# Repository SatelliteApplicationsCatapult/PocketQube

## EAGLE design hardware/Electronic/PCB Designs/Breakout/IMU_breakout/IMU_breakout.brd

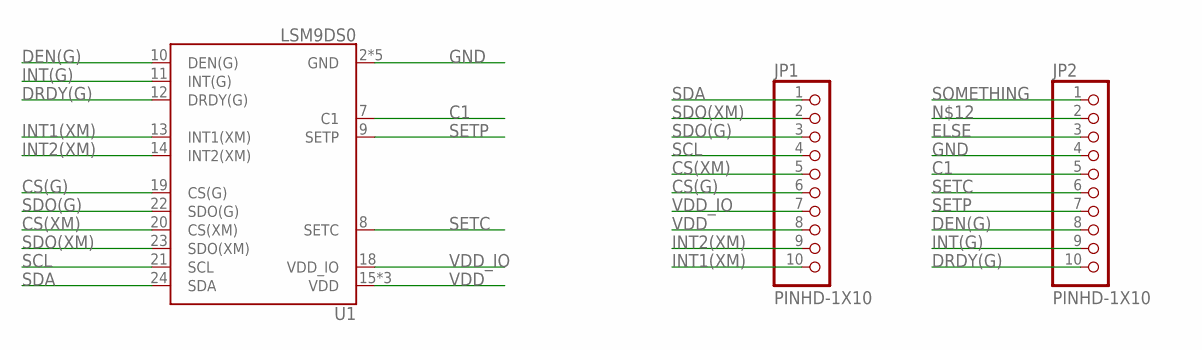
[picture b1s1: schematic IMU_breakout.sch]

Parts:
JP1, JP2: PINHD-1X10; 1X10-BIG
U1: LSM9DS0; LGA-24

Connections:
C1: JP2.5, U1.7 (C1)
CS(G): JP1.6, U1.19 (CS(G))
CS(XM): JP1.5, U1.20 (CS(XM))
DEN(G): JP2.8, U1.10 (DEN(G))
DRDY(G): JP2.10, U1.12 (DRDY(G))
ELSE: JP2.3
GND: JP2.4, U1.2 (GND), U1.3 (GND), U1.4 (GND), U1.5 (GND), U1.6 (GND)
INT1(XM): JP1.10, U1.13 (INT1(XM))
INT2(XM): JP1.9, U1.14 (INT2(XM))
INT(G): JP2.9, U1.11 (INT(G))
SCL: JP1.4, U1.21 (SCL)
SDA: JP1.1, U1.24 (SDA)
SDO(G): JP1.3, U1.22 (SDO(G))
SDO(XM): JP1.2, U1.23 (SDO(XM))
SETC: JP2.6, U1.8 (SETC)
SETP: JP2.7, U1.9 (SETP)
SOMETHING: JP2.1
VDD: JP1.8, U1.15 (VDD), U1.16 (VDD), U1.17 (VDD)
VDD_IO: JP1.7, U1.18 (VDD_IO)

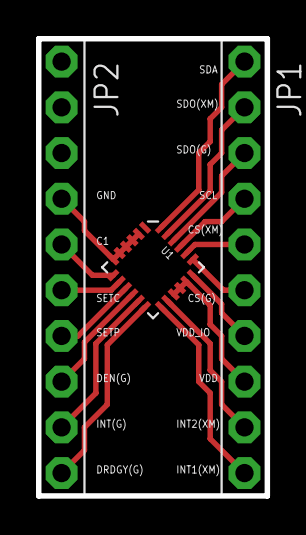
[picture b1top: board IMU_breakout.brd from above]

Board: 2 copper layers, 12.7 x 25.4 mm, 3 parts (0 on the bottom side), 17 nets.

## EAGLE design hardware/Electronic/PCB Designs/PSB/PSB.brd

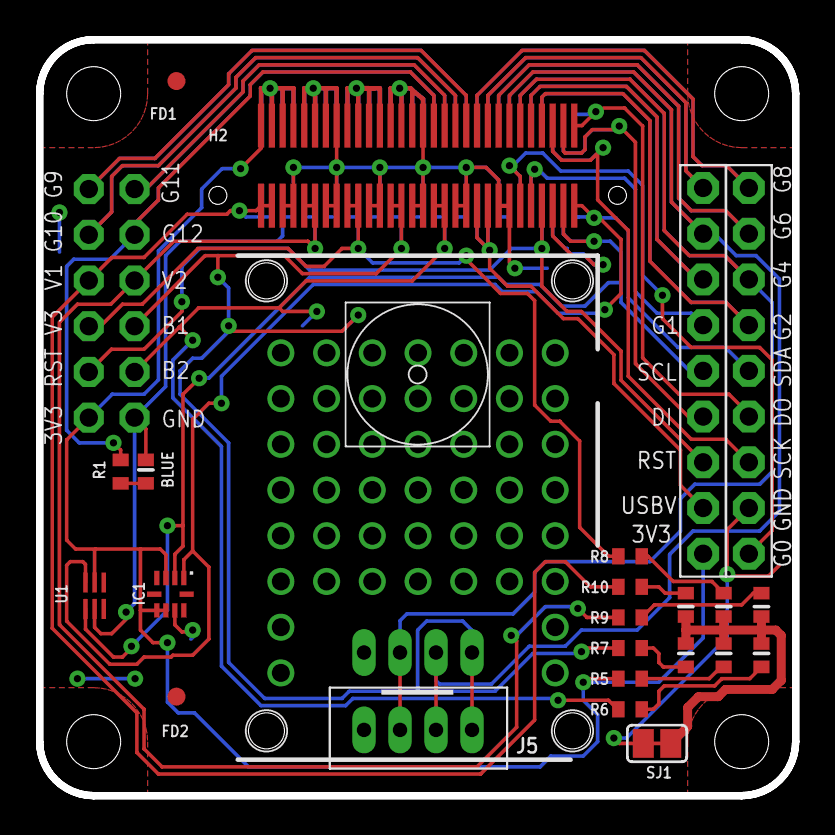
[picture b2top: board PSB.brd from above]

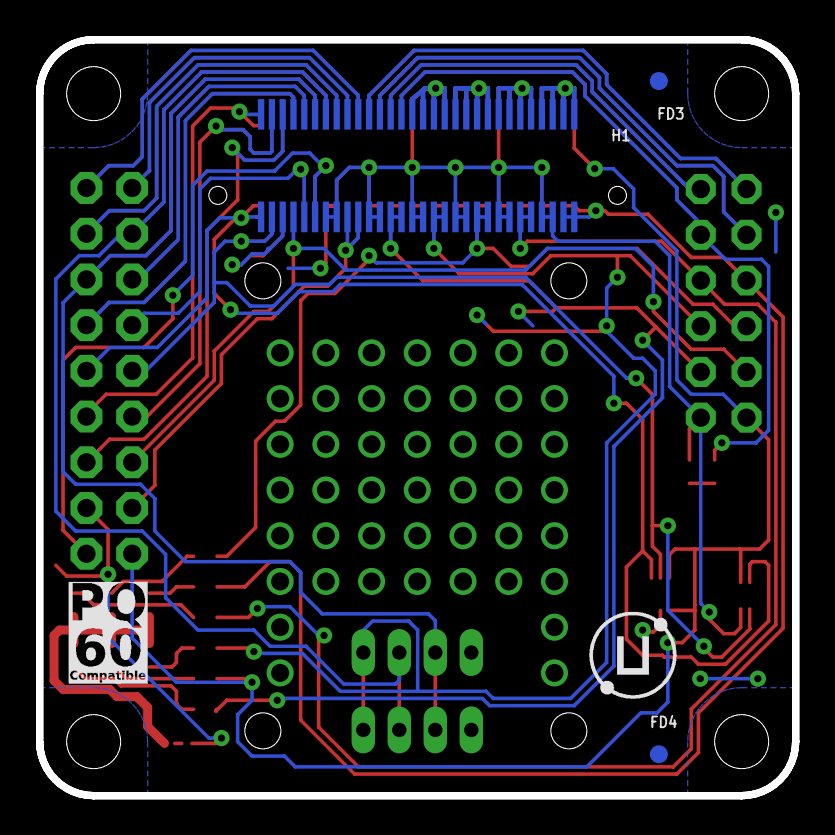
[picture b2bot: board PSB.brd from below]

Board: 2 copper layers, 42.0 x 42.0 mm, 31 parts (5 on the bottom side), 36 nets.

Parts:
BLUE: LED-0402; 0402-LED
FD1, FD2, FD3, FD4: FIDUCIAL; FIDUCIAL_1MM
GREEB@2: LED-0402; 0402-LED
GREEN@1, GREEN@3: LED-0402; 0402-LED
H1: FX8C-060S-SV(92)
H2: FX8C-060P-SV(92)
IC1: SI1146; QFN-10
J5, J6: JST-PH_4-PIN_HEADER; JST_B4B-PH_HEADER
JP1: 2X06-CLEANBIG
JP2, JP5: 1X09-BIG
R1, R5, R8, R9, R10: 220R; R0402
R6, R7: 330R; R0402
RED: LED-0402; 0402-LED
SJ1: SJ
U1: TMP102AIDRLT; SOT50P160X60-6N
U$1: SA_LOGO_SMALL
U$2: UBO_LOGO
U$3: PQ60_CMP
YELLOW@1, YELLOW@2: LED-0402; 0402-LED

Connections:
+3V3: H1.P$57, H1.P$58, H1.P$59, H1.P$60, H2.P$57, H2.P$58, H2.P$59, H2.P$60, IC1.3, IC1.6, IC1.7, JP1.11, JP5.9, R5.2, U1.5
+3V3_SW1: H1.P$1, H1.P$2, H2.P$1, H2.P$2, JP1.5, R10.2
+3V3_SW2: H1.P$5, H1.P$6, H2.P$5, H2.P$6, JP1.6, R9.2
+3V3_SW3: H1.P$9, H1.P$10, H2.P$9, H2.P$10, JP1.7, R8.2
BATV: H1.P$49, H1.P$50, H1.P$51, H1.P$52, H2.P$49, H2.P$50, H2.P$51, H2.P$52
BATV_SW1: H1.P$13, H1.P$14, H2.P$13, H2.P$14, J5.P4, J6.P4, JP1.8, R7.2
BATV_SW2: H1.P$17, H1.P$18, H2.P$17, H2.P$18, JP1.10, R6.2
GND: BLUE.C, H1.P$3, H1.P$4, H1.P$7, H1.P$8, H1.P$11, H1.P$12, H1.P$15, H1.P$16, H1.P$19, H1.P$20, H1.P$23, H1.P$24, H1.P$28, H1.P$45, H1.P$46, H1.P$47, H1.P$48, H1.P$53, H1.P$54, H1.P$55, H1.P$56, H2.P$3, H2.P$4, H2.P$7, H2.P$8, H2.P$11, H2.P$12, H2.P$15, H2.P$16, H2.P$19, H2.P$20, H2.P$23, H2.P$24, H2.P$28, H2.P$45, H2.P$46, H2.P$47, H2.P$48, H2.P$53, H2.P$54, H2.P$55, H2.P$56, IC1.8, J5.P1, J6.P1, JP1.12, JP2.8, SJ1.2, U1.2, U1.4
GPIO0: H1.P$25, H2.P$25, JP2.9
GPIO1: H1.P$26, H2.P$26, JP5.4
GPIO2: H1.P$34, H2.P$34, JP2.4
GPIO3: H1.P$35, H2.P$35, JP5.3
GPIO4: H1.P$36, H2.P$36, J5.P2, J6.P2, JP2.3
GPIO5: H1.P$37, H2.P$37, J5.P3, J6.P3, JP5.2
GPIO6: H1.P$38, H2.P$38, JP2.2
GPIO7: H1.P$39, H2.P$39, JP5.1
GPIO8: H1.P$40, H2.P$40, JP2.1
GPIO9: H1.P$41, H2.P$41, JP1.1
GPIO10: H1.P$42, H2.P$42, JP1.3
GPIO11: H1.P$43, H2.P$43, JP1.2
GPIO12: H1.P$44, H2.P$44, JP1.4, R1.2
MISO: H1.P$32, H2.P$32, JP5.6
MOSI: H1.P$31, H2.P$31, JP2.6
unnamed: BLUE.A, R1.1
unnamed: GREEN@1.A, R10.1
unnamed: GREEB@2.A, R9.1
unnamed: GREEN@3.A, R8.1
unnamed: R7.1, YELLOW@1.A
unnamed: R6.1, YELLOW@2.A
unnamed: R5.1, RED.A
unnamed: GREEB@2.C, GREEN@1.C, GREEN@3.C, RED.C, SJ1.1, YELLOW@1.C, YELLOW@2.C
RESET: H1.P$27, H2.P$27, JP1.9, JP5.7
SCK: H1.P$33, H2.P$33, JP2.7
SCL: H1.P$29, H2.P$29, IC1.2, JP5.5, U1.1
SDA: H1.P$30, H2.P$30, IC1.1, JP2.5, U1.6
USB_VBUS: H1.P$21, H1.P$22, H2.P$21, H2.P$22, JP5.8

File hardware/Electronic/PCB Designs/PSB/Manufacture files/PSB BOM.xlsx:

Qty | Value | Device | Package | Parts | Description | Supplier | Order code | Price per | Total | Notes
2 |  | PINHD-1X9 | 1X09-BIG | JP2, JP5 | Pin header 1x10 0.1 spacing" |  |  |  | 0 | Do not populate
1 |  | PINHD-2X6 | 2X06-CLEANBIG | JP1 | PIN HEADER |  |  |  | 0 | Do not populate
1 |  | SJ | SJ | SJ1 | SMD solder JUMPER |  |  |  | 0 | Do not populate
5 | 220R | R-EU_R0402 | R0402 | R1, R5, R8, R9, R10 | RESISTOR, European symbol |  |  |  | 0
2 | 330R | R-EU_R0402 | R0402 | R6, R7 | RESISTOR, European symbol |  |  |  | 0
4 | FIDUCIAL | FIDUCIAL | FIDUCIAL_1MM | FD1, FD2, FD3, FD4 | For use by pick and place machines to calibrate the vision/machine, 1mm |  |  |  | 0 | Do not populate
1 | FX8C-060P-SV(91) | FX8C-060P-SV(91) | FX8C-060P-SV(91) | H2 |  |  |  |  | 0 | Do not populate
1 | FX8C-060P-SV(91) | FX8C-060P-SV(91) | FX8C-060S-SV(91) | H1 |  | Farnell |  | 2.7515999999999998 | 77.044799999999995 | Other suppliers available
1 | JST-PH_4-PIN_HEADER | JST-PH_4-PIN_HEADER | JST_B4B-PH_HEADER | J5 | 4-pin JST PH Shrouded Header, top entry | Farnell | 9492437 | 0.112 | 11.200000000000001 | Other suppliers available
1 | JST-PH_4-PIN_HEADER | JST-PH_4-PIN_HEADER | JST_B4B-PH_HEADER | J6 | 4-pin JST PH Shrouded Header, top entry |  |  |  | 0 | Do not populate
1 | LED-0402 | LED-0402 | 0402-LED | BLUE |  |  |  |  | 0 | Any 0402 blue LED
3 | LED-0402 | LED-0402 | 0402-LED | GREEB@2, GREEN@1, GREEN@3 |  |  |  |  | 0 | Any 0402 green LED
1 | LED-0402 | LED-0402 | 0402-LED | RED |  |  |  |  | 0 | Any 0402 red LED
2 | LED-0402 | LED-0402 | 0402-LED | YELLOW@1, YELLOW@2 |  |  |  |  | 0 | Any 0402 yellow LED
1 | SI1146 | SI1146 | QFN-10 | IC1 | PROXIMITY/UV/AMBIENT LIGHT SENSOR IC WITH I2C INTERFACE | Digikey | 336-2623-1-ND | 3.1135999999999999 | 87.180800000000005 | Available from other suppliers, but must be A10 variant
1 | TMP102AIDRLT | TMP102AIDRLT | SOT50P160X60-6N | U1 | Temperature Sensor | Farnell | 1652477 | 1 | 28 | Available from other suppliers
 |  |  |  |  |  |  |  |  | 203.4256

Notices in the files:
hardware/Electronic/PCB Designs/PSB/PSB.brd:
Copyright 2019 Satellite Applications Catapult
parts and their libraries:
SparkFun-DigitalIC: Licensing: Creative Commons ShareAlike 4.0 International - https://creativecommons.org/licenses/by-sa/4.0
